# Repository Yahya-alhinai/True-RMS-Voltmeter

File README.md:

# True RMS Voltmeter
 
Construct a true RMS voltmeter appropriate for measuring voltages between 0.1mV-RMS and 1mV-RMS in the bandwidth between 10Hz and 10kHZ which aimed to monitor human heart rate by measuring the electric pulses in real time. Your system should incorporate a 24 bit analog to digital converter (ADC) and a microcontroller for computation and display purposes.

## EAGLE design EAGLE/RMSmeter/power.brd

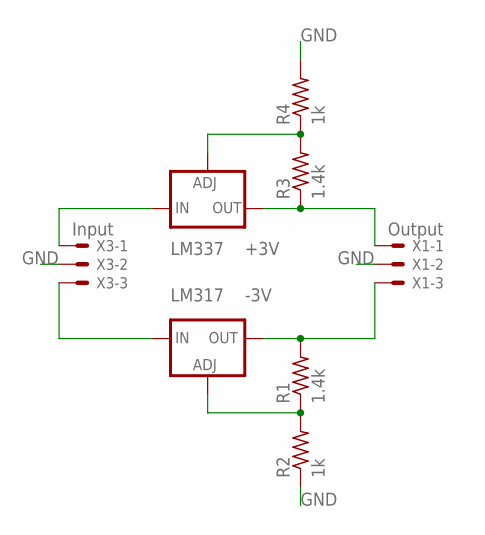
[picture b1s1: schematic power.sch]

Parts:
LM317: -3V; 317TL
LM337: +3V; 337TL
R1, R3: 1.4k; 0204/7
R2, R4: 1k; 0204/7
X1: Output; 22-23-2031
X3: Input; 22-23-2031

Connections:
GND: R2.1, R4.2, X1.2, X3.2
unnamed: LM317.2 (OUT), R1.2, X1.3
unnamed: LM337.3 (OUT), R3.1, X1.1
unnamed: LM337.2 (IN), X3.1
unnamed: LM317.3 (IN), X3.3
unnamed: LM337.1 (ADJ), R3.2, R4.1
unnamed: LM317.1 (ADJ), R1.1, R2.2

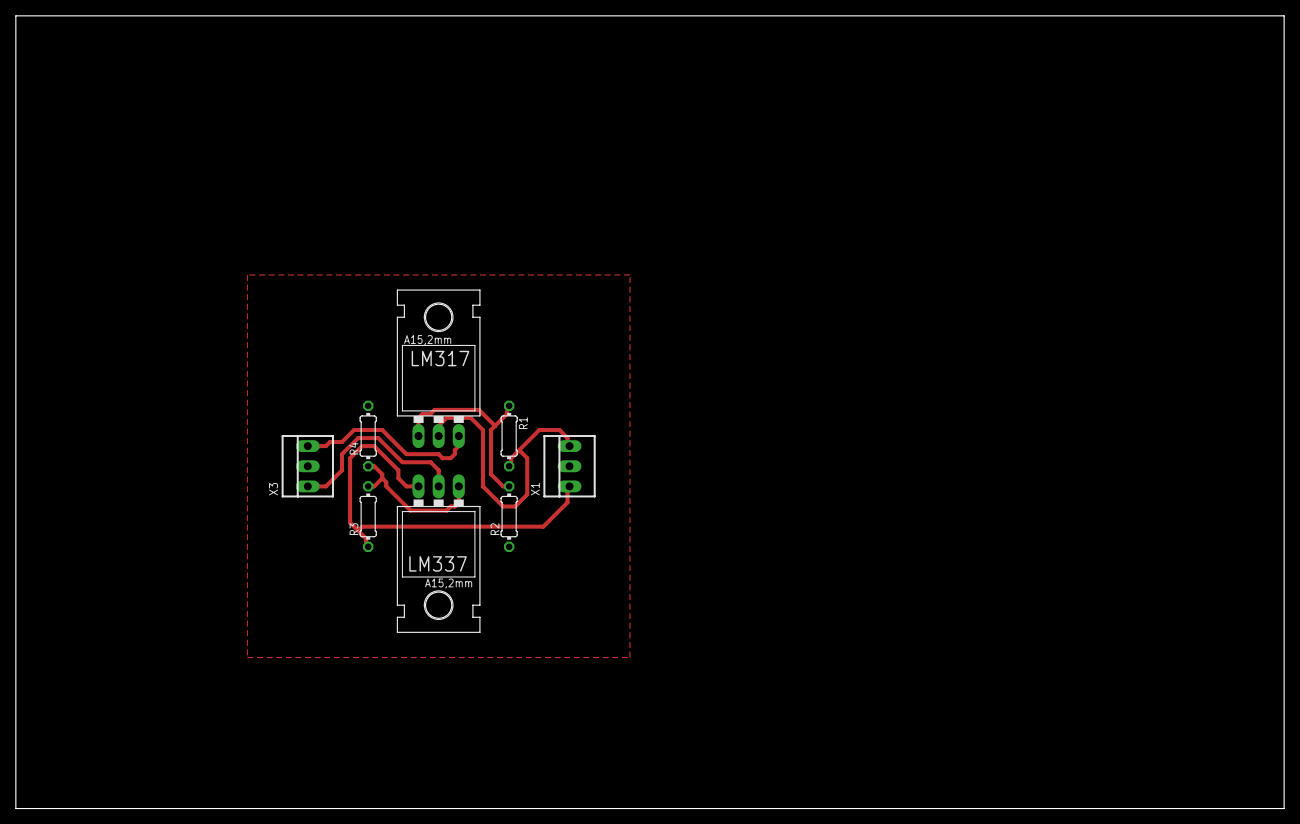
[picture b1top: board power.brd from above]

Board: 2 copper layers, 160.0 x 100.0 mm, 8 parts (0 on the bottom side), 7 nets.

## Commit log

2020-07-08 Final
